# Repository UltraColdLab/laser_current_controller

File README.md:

# laser_current_controller
laser current controller JILA

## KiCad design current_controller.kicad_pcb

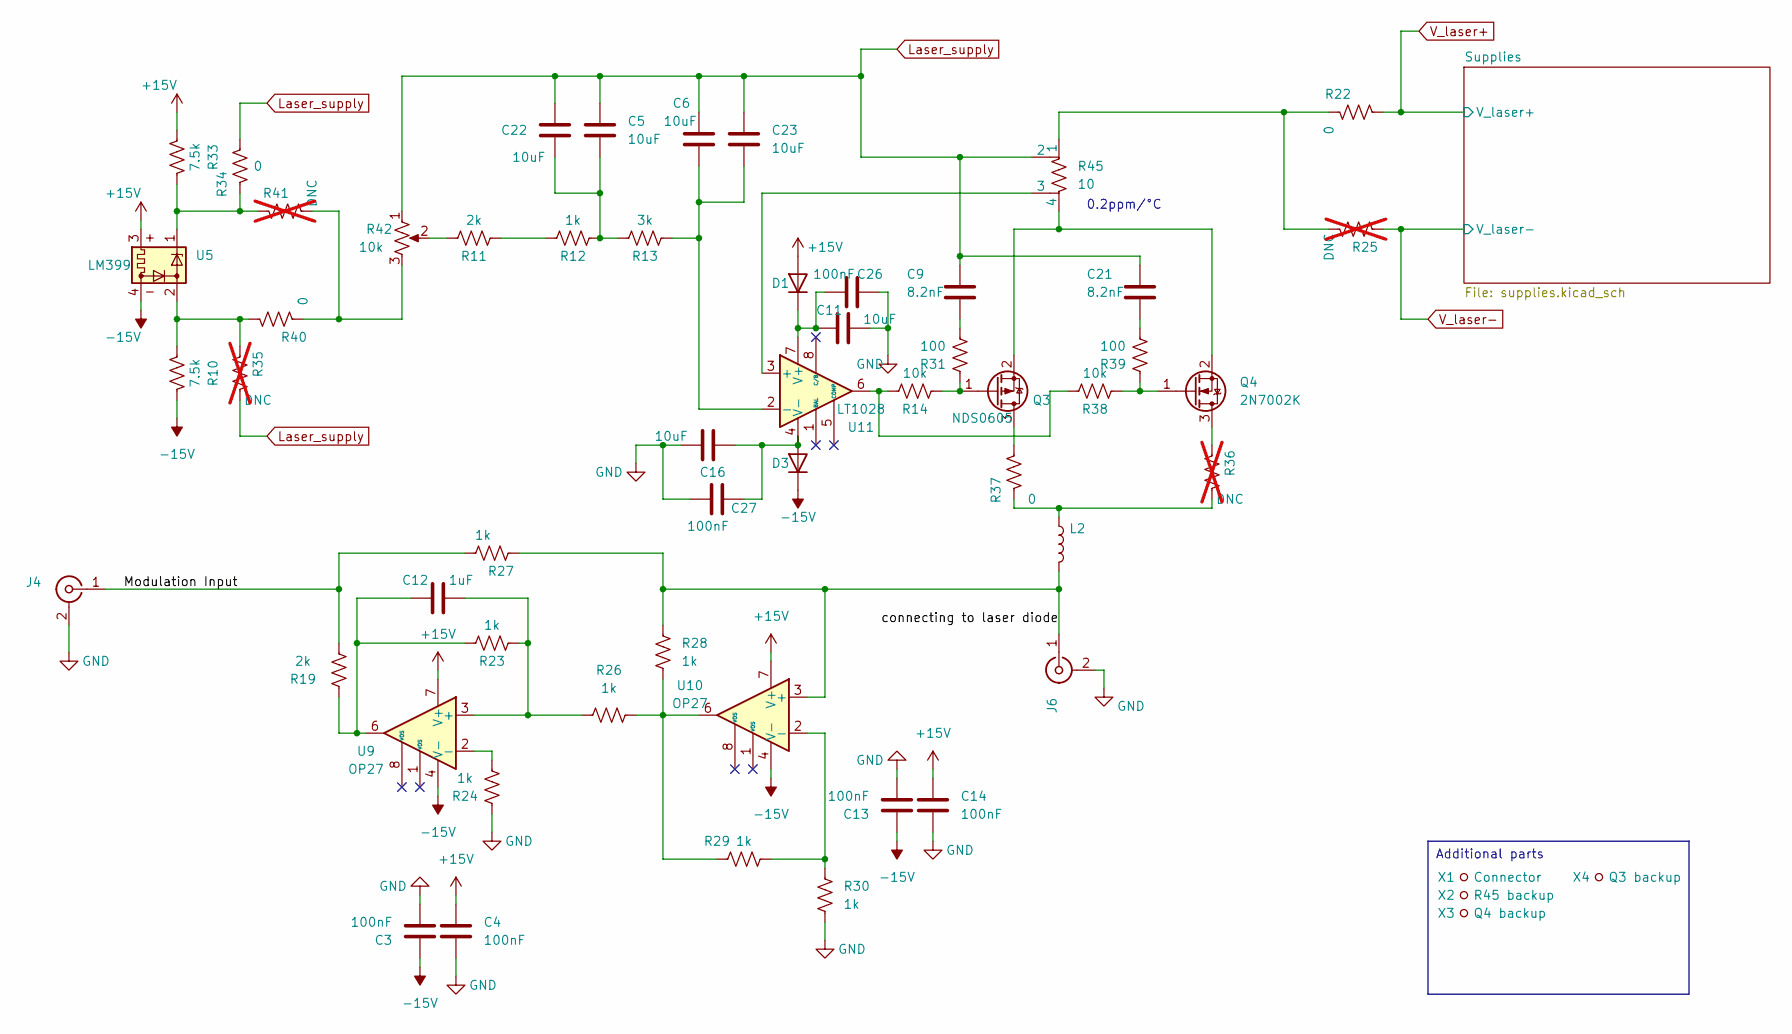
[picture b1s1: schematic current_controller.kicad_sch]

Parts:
C3, C4, C13, C14, C26, C27: 100nF; C_0603_1608Metric; MPN CL10B104KB8NNWC; DIGIKEY 1276-1935-1-ND
C5, C6, C22, C23: 10uF; C_0603_1608Metric; MPN ZRB18AR61E106ME01L; DIGIKEY 490-10991-1-ND
C9, C21: 8.2nF; C_0603_1608Metric; MPN C0603C822K5RAC7867; DIGIKEY 399-C0603C822K5RAC7867CT-ND
C11, C16: 10uF; C_1210_3225Metric; MPN CC1210ZKY5V9BB106; DIGIKEY 311-3470-1-ND
C12: 1uF; C_0603_1608Metric; MPN CC0603KRX5R8BB105; DIGIKEY 311-1445-1-ND
D1, D3: 1N4007; D_SOD-123F; MPN 1N4007FL; DIGIKEY 1655-1N4007FLCT-ND
J4, J6: Modulation Input; BNC_Amphenol_B6252HB-NPP3G-50_Horizontal; MPN 5227161-7; DIGIKEY A32260-ND
L2: 100uH; Inductor_2220; MPN B82442T1104K050; DIGIKEY 495-5657-1-ND - Cut Tape (CT)
Q3: NDS0605; SOT-23-3; MPN NDS0605; DIGIKEY NDS0605CT-ND
Q4: 2N7002K; SOT-23-3; MPN 2N7002K; DIGIKEY 2N7002KCT-ND
R10, R33: 7.5k; R_0805_2012Metric; MPN RNCP0805FTD7K50; DIGIKEY RNCP0805FTD7K50CT-ND
R11, R19: 2k; R_0805_2012Metric; MPN RG2012P-202-B-T5; DIGIKEY RG20P2.0KBCT-ND
R12, R23, R24, R26, R27, R28, R29, R30: 1k; R_0805_2012Metric; MPN ERA-6AEB102V; DIGIKEY P1.0KDACT-ND
R13: 3k; R_0805_2012Metric; MPN ERA-6AEB302V; DIGIKEY P3.0KDACT-ND
R14, R38: 10k; R_0805_2012Metric; MPN RG2012P-103-B-T5; DIGIKEY RG20P10.0KBCT-ND
R22, R34, R37, R40: 0; R_0805_2012Metric; MPN RMCF0805ZT0R00; DIGIKEY RMCF0805ZT0R00CT-ND
R25, R35, R36, R41: DNC; R_0805_2012Metric; not fitted
R31, R39: 100; R_0805_2012Metric; MPN RG2012P-101-B-T5; DIGIKEY RG20P100BCT-ND
R42: 10k; Multi_turn_potentiometer; MPN 8146R10KL.25; DIGIKEY 987-1541-ND
R45: 10; 10 Ohms VPG Foil Resistors Y160610R0000D9W; MPN Y160610R0000D9W; DIGIKEY 804-1191-ND
U5: LM399; Analog_TO-46-4_ThermalShield; MPN LM399AH#PBF; DIGIKEY 505-LM399AH#PBF-ND
U9, U10: OP27; SOIC-8_3.9x4.9mm_P1.27mm; MPN OP27GSZ-REEL; DIGIKEY OP27GSZ-REELCT-ND
U11: LT1028; SOIC-8_3.9x4.9mm_P1.27mm; MPN LT1028CS8#TRPBF; DIGIKEY LT1028CS8#TRPBFCT-ND
X1: Connector; MPN 1984028; DIGIKEY 277-1707-ND
X2: R45 backup; TO-220-4_Horizontal_TabDown; MPN Y212350R0000B9L; DIGIKEY 804-1090-ND
X3: Q4 backup; SOT-23-3; MPN SSM3K341R,LF; DIGIKEY SSM3K341RLFCT-ND
X4: Q3 backup; SOT-23-3; MPN SSM3J168F,LF; DIGIKEY SSM3J168FLFCT-ND

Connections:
+15V: C4.1, C14.1, D1.2 (A), R33.2, U5.3, U9.7 (V+), U10.7 (V+); also elsewhere on the board
-15V: C3.1, C13.1, D3.1 (K), R10.1, U5.4, U9.4 (V-), U10.4 (V-); also elsewhere on the board
/Modulation Input: J4.1 (In), R19.2, R27.2
/connecting to laser diode: J6.1 (In), L2.2, R27.1, R28.2, U10.3 (+)
GND: C3.2, C4.2, C11.2, C13.2, C14.2, C16.2, C26.2, C27.1, J4.2 (Ext), J6.2 (Ext), R24.1, R30.1; also elsewhere on the board
Laser_supply: C5.1, C6.1, C9.1, C21.1, C22.2, C23.1, R34.1, R35.2, R42.1, R45.2
unnamed: C9.2, R31.2
unnamed: C12.1, R19.1, R23.1, U9.6
unnamed: C21.2, R39.2
unnamed: C5.2, C22.1, R12.2, R13.1
unnamed: C11.1, C26.1, D1.1 (K), U11.7 (V+)
unnamed: C16.1, C27.2, D3.2 (A), U11.4 (V-)
unnamed: L2.1, R36.2, R37.2
unnamed: Q3.3 (D), R37.1
unnamed: Q3.1 (G), R14.2, R31.1
unnamed: Q3.2 (S), Q4.2 (S), R45.4
unnamed: Q4.3 (D), R36.1
unnamed: Q4.1 (G), R38.2, R39.1
unnamed: R10.2, R35.1, R40.1, U5.2
unnamed: R11.1, R42.2
unnamed: R11.2, R12.1
unnamed: R14.1, R38.1, U11.6
unnamed: R22.2, R25.2, R45.1
unnamed: R26.2, R28.1, R29.1, U10.6
unnamed: R33.1, R34.2, R41.1, U5.1
unnamed: R40.2, R41.2, R42.3
unnamed: C12.2, R23.2, R26.1, U9.3 (+)
unnamed: R24.2, U9.2 (-)
unnamed: R29.2, R30.2, U10.2 (-)
unnamed: R45.3, U11.3 (+)
unnamed: C6.2, C23.2, R13.2, U11.2 (-)
V_laser+: R22.1; also elsewhere on the board
V_laser-: R25.1; also elsewhere on the board

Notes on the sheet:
Additional parts
0.2ppm/°C

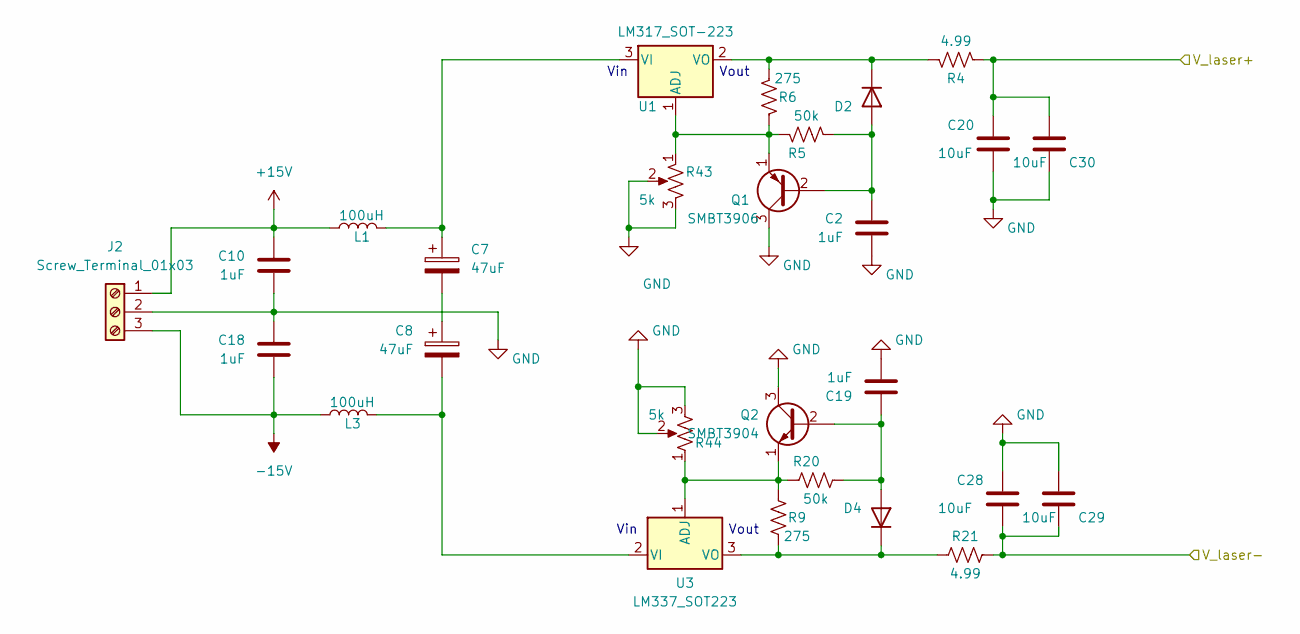
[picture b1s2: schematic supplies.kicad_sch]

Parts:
C2, C10, C18, C19: 1uF; C_0603_1608Metric; MPN CC0603KRX5R8BB105; DIGIKEY 311-1445-1-ND
C7, C8: 47uF; CP_EIA-3216-10_Kemet-I; MPN T495X476M035ATE300; DIGIKEY 399-10312-1-ND
C20, C28, C29, C30: 10uF; C_1210_3225Metric; MPN CC1210ZKY5V9BB106; DIGIKEY 311-3470-1-ND
D2, D4: 1N914WT; D_SOD-523F; MPN 1N914BWT; DIGIKEY 1N914BWTCT-ND
J2: Screw_Terminal_01x03; TerminalBlock_4Ucon_1x03_P3.50mm_Horizontal; MPN 1945106; DIGIKEY 277-1750-ND
L1, L3: 100uH; L_12x12mm_H8mm; MPN 74477020; DIGIKEY 732-1235-1-ND
Q1: SMBT3906; SOT-23-3; MPN SMBT3906E6327HTSA1; DIGIKEY SMBT3906E6327HTSA1CT-ND
Q2: SMBT3904; SOT-23-3; MPN MMBT3904_R1_00001; DIGIKEY 3757-MMBT3904_R1_00001CT-ND
R4, R21: 4.99; R_0805_2012Metric; MPN CRCW08054R99FKEA; DIGIKEY 541-4.99CCCT-ND
R5, R20: 50k; R_0805_2012Metric; MPN MCU08050D5002BP100; DIGIKEY 749-MCU08050D5002BP100CT-ND
R6, R9: 275; R_0805_2012Metric; MPN RC0805FR-07274RL; DIGIKEY 311-274CRCT-ND
R43, R44: 5k; Potentiometer_Bourns_3296W_Vertical; MPN 3296W-1-502LF; DIGIKEY 3296W-502LF-ND
U1: LM317_SOT-223; SOT-223-3_TabPin2; MPN LM317EMP/NOPB; DIGIKEY LM317EMP/NOPBCT-ND
U3: LM337_SOT223; SOT-223-3_TabPin2; MPN LM337IMP/NOPB; DIGIKEY LM337IMP/NOPBCT-ND

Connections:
+15V: C10.1, J2.1, L1.2; also elsewhere on the board
-15V: C18.2, J2.3, L3.2; also elsewhere on the board
GND: C2.2, C10.2, C18.1, C19.2, C20.2, C28.1, C29.1, C30.2, J2.2, Q1.3 (C), Q2.3 (C), R43.2, R43.3, R44.2, R44.3; also elsewhere on the board
unnamed: C7.2, C8.1
unnamed: C2.1, D2.2 (A), Q1.2 (B), R5.1
unnamed: D2.1 (K), R4.2, R6.2, U1.2 (VO)
unnamed: C19.1, D4.2 (A), Q2.2 (B), R20.1
unnamed: D4.1 (K), R9.2, R21.2, U3.3 (VO)
unnamed: Q1.1 (E), R5.2, R6.1, R43.1, U1.1 (ADJ)
unnamed: Q2.1 (E), R9.1, R20.2, R44.1, U3.1 (ADJ)
unnamed: C7.1, L1.1, U1.3 (VI)
unnamed: C8.2, L3.1, U3.2 (VI)
V_laser+: C20.1, C30.1, R4.1; also elsewhere on the board
V_laser-: C28.2, C29.2, R21.1; also elsewhere on the board

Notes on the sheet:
Vout
Vin

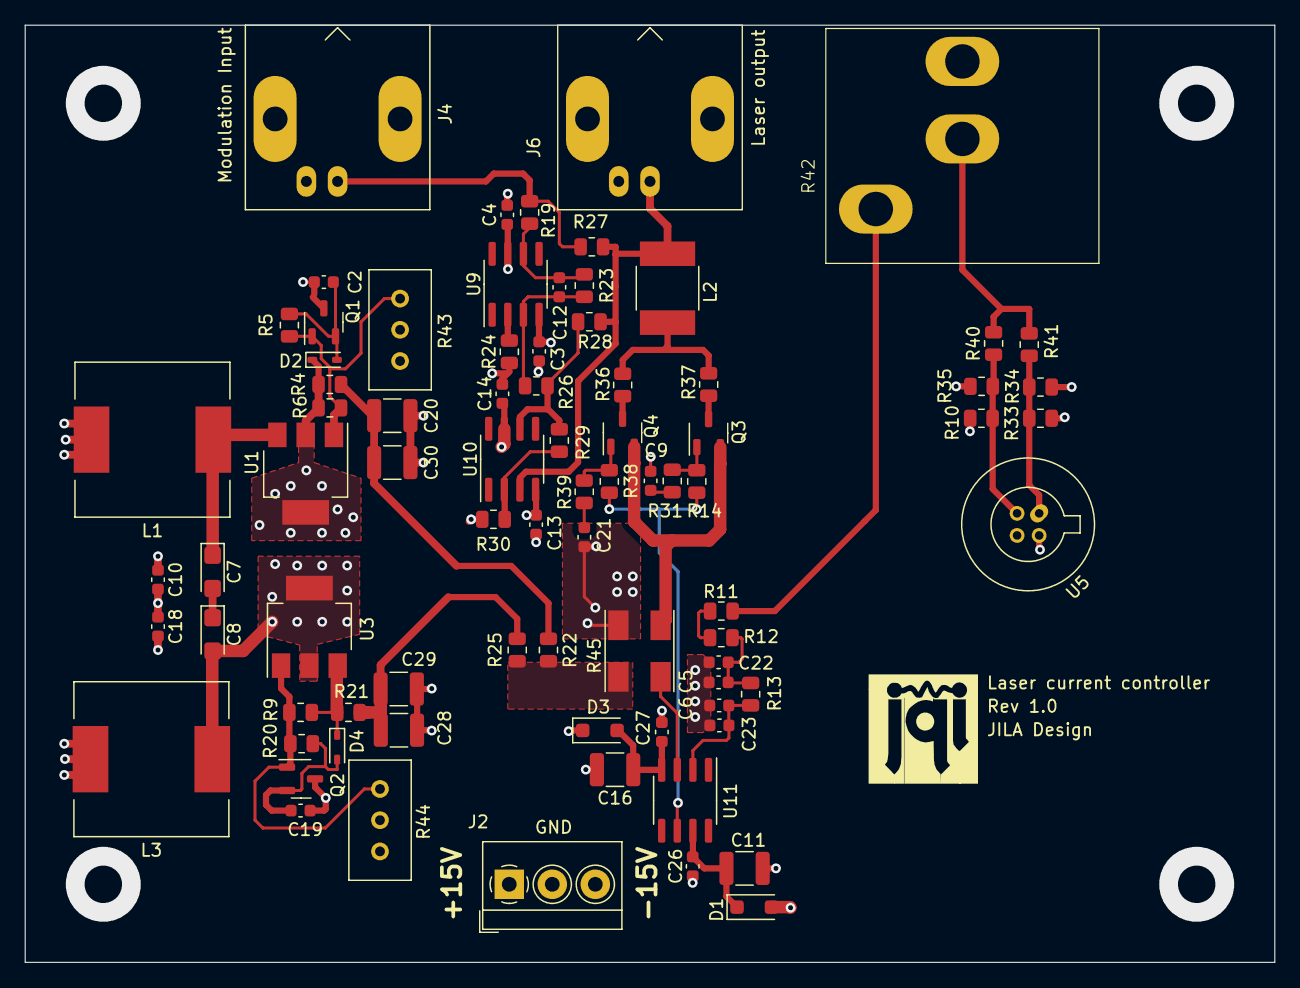
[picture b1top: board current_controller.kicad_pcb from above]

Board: 4 copper layers, 101.6 x 76.2 mm, 81 parts (0 on the bottom side), 42 nets.

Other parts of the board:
U$3: JQI_LOGO_NEGATIVE-SILKSCREEN

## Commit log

2024-05-06 Add files via upload
    JILA design, A low-noise high-speed diode laser current controller, Rev. Sci. Instrum., Vol. 64, No. 6, August 1993.
    Note: 1. The polarities of the Opamps are wrong;
    2. Footprint of the trimpot doesn't match the actual one,
    3. We changed some of the capacitors, such as 2uF
    4. we also changed the capacitor of C21
    5. This only applied to negative current.
